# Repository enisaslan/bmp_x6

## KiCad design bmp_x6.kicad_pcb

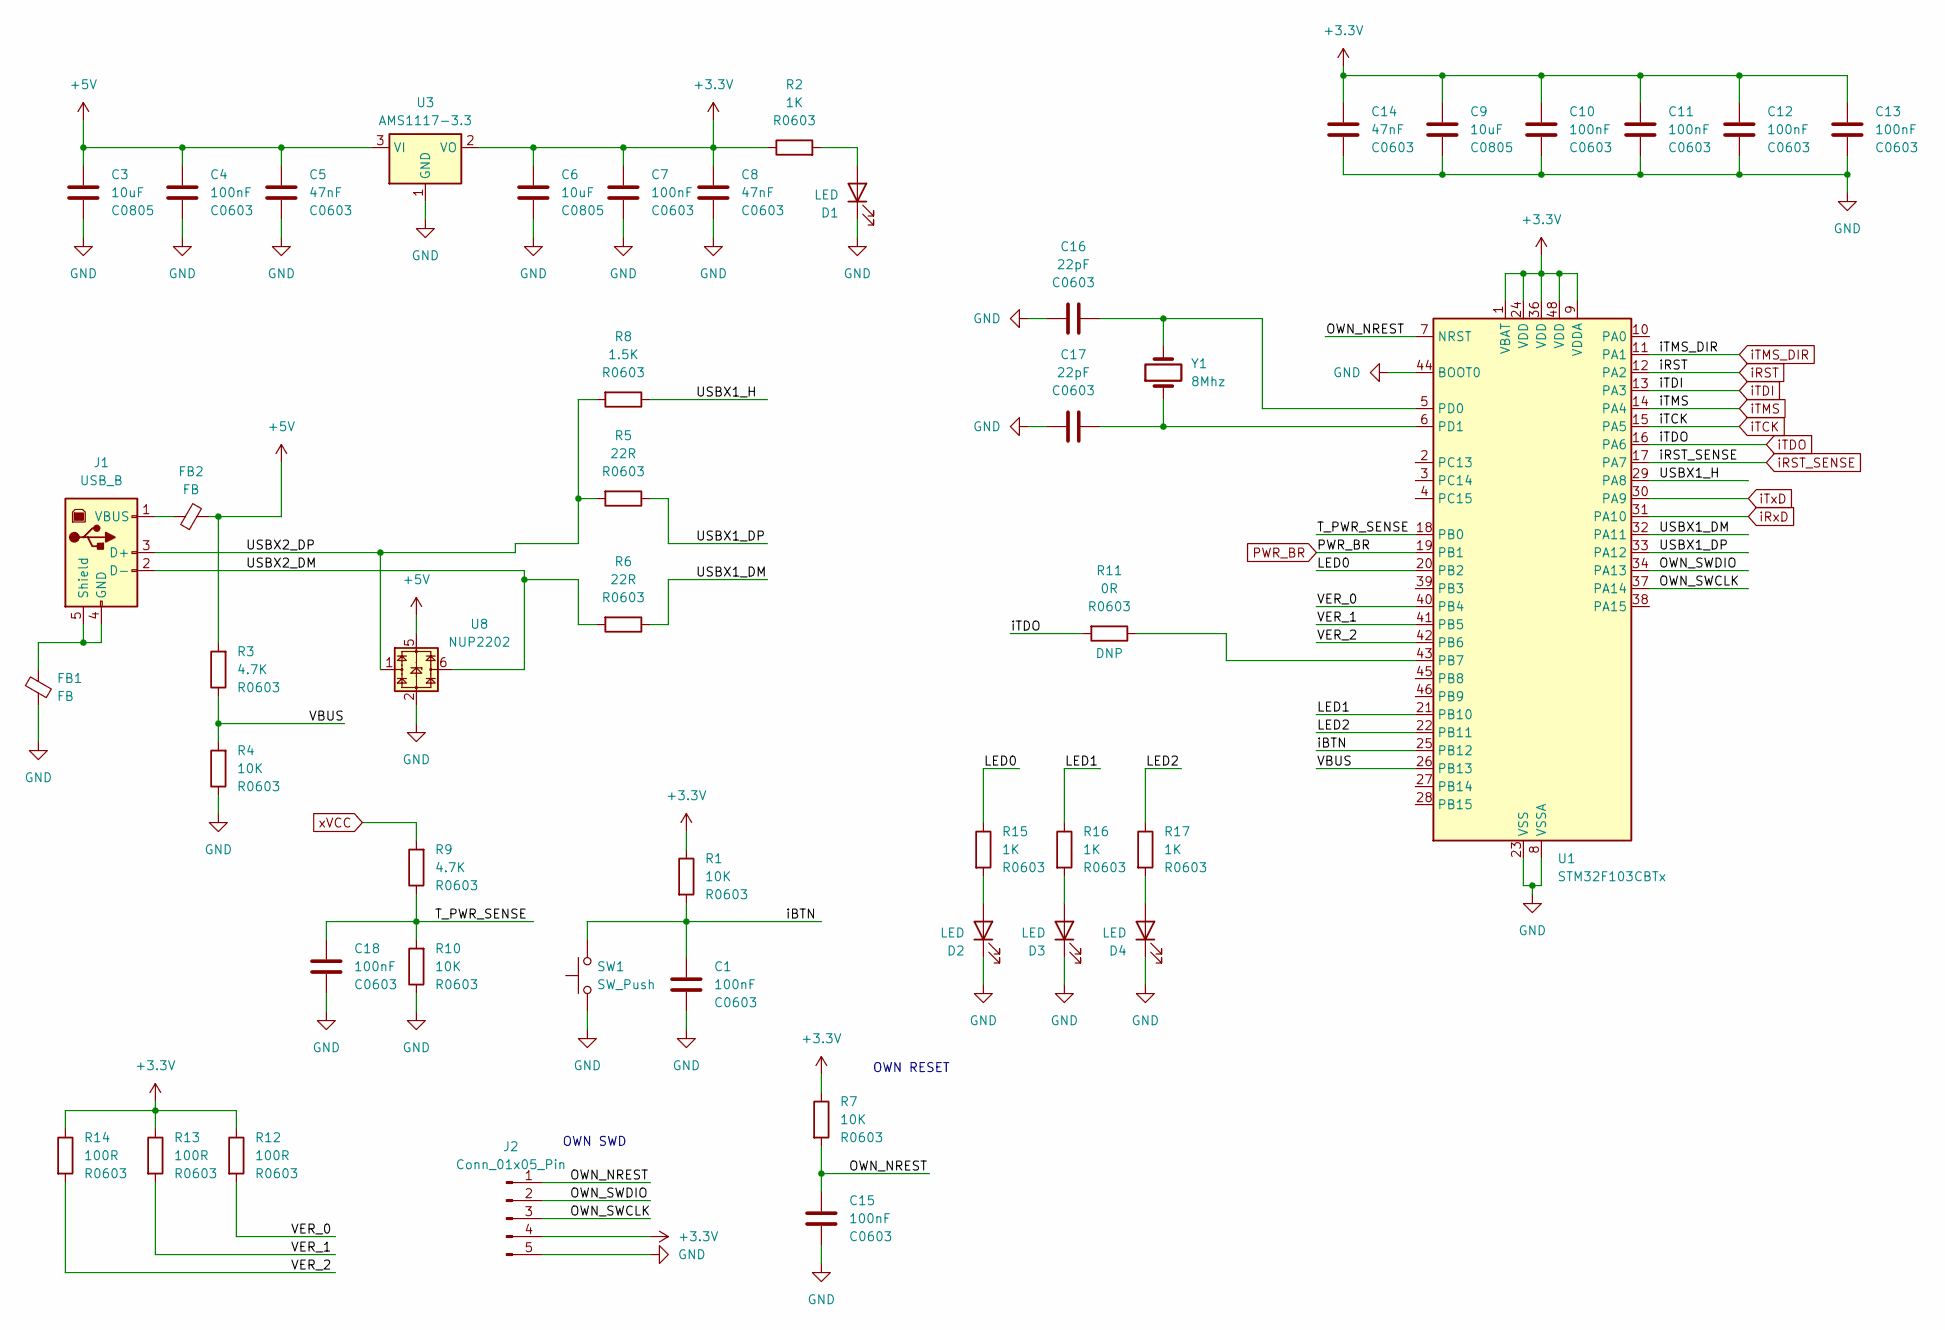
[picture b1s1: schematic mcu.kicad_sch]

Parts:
C1, C4, C7, C10, C11, C12, C13, C15, C18: 100nF; C_0603_1608Metric
C3, C6, C9: 10uF; C_0805_2012Metric
C5, C8, C14: 47nF; C_0603_1608Metric
C16, C17: 22pF; C_0603_1608Metric
D1, D2, D3, D4: LED; LED_0805_2012Metric
FB1, FB2: FB; L_0603_1608Metric
J1: USB_B; USB_B_Lumberg_2411_02_Horizontal
J2: Conn_01x05_Pin; PinHeader_1x05_P2.54mm_Vertical
R1, R4, R7, R10: 10K; R_0603_1608Metric
R2, R15, R16, R17: 1K; R_0603_1608Metric
R3, R9: 4.7K; R_0603_1608Metric
R5, R6: 22R; R_0603_1608Metric
R8: 1.5K; R_0603_1608Metric
R11: 0R; R_0603_1608Metric
R12, R13, R14: 100R; R_0603_1608Metric
SW1: SW_Push; SW_Tactile_SPST_Angled_PTS645Vx58-2LFS
U1: STM32F103CBTx; LQFP-48_7x7mm_P0.5mm
U3: AMS1117-3.3; SOT-223-3_TabPin2
U8: NUP2202; SOT-363_SC-70-6
Y1: 8Mhz; Crystal_SMD_Abracon_ABM3-2Pin_5.0x3.2mm

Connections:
+3.3V: C6.1, C7.1, C8.1, C9.1, C10.1, C11.1, C12.1, C13.1, C14.1, J2.4, R1.1, R2.1, R7.1, R12.1, R13.1, R14.1, U1.1 (VBAT), U1.9 (VDDA), U1.24 (VDD), U1.36 (VDD), U1.48 (VDD), U3.2 (VO); also elsewhere on the board
+5V: C3.1, C4.1, C5.1, FB2.2, R3.2, U3.3 (VI), U8.5
/mcu/LED0: R15.1, U1.20 (PB2)
/mcu/LED1: R16.1, U1.21 (PB10)
/mcu/LED2: R17.1, U1.22 (PB11)
/mcu/OWN_NREST: C15.1, J2.1, R7.2, U1.7 (NRST)
/mcu/OWN_SWCLK: J2.3, U1.37 (PA14)
/mcu/OWN_SWDIO: J2.2, U1.34 (PA13)
/mcu/T_PWR_SENSE: C18.1, R9.1, R10.2, U1.18 (PB0)
/mcu/USBX1_DM: R6.1, U1.32 (PA11)
/mcu/USBX1_DP: R5.1, U1.33 (PA12)
/mcu/USBX1_H: R8.1, U1.29 (PA8)
/mcu/USBX2_DM: J1.2 (D-), R6.2, U8.6
/mcu/USBX2_DP: J1.3 (D+), R5.2, R8.2, U8.1
/mcu/VBUS: R3.1, R4.2, U1.26 (PB13)
/mcu/VER_0: R12.2, U1.40 (PB4)
/mcu/VER_1: R13.2, U1.41 (PB5)
/mcu/VER_2: R14.2, U1.42 (PB6)
/mcu/iBTN: C1.1, R1.2, SW1.2, U1.25 (PB12)
GND: C1.2, C3.2, C4.2, C5.2, C6.2, C7.2, C8.2, C9.2, C10.2, C11.2, C12.2, C13.2, C14.2, C15.2, C16.2, C17.2, C18.2, D1.1 (K), D2.1 (K), D3.1 (K), D4.1 (K), FB1.2, J2.5, R4.1, R10.1, SW1.1, U1.8 (VSSA), U1.23 (VSS), U1.35 (VSS), U1.44 (BOOT0), U1.47 (VSS), U3.1 (GND), U8.2; also elsewhere on the board
unnamed: D1.2 (A), R2.2
unnamed: D2.2 (A), R15.2
unnamed: D3.2 (A), R16.2
unnamed: D4.2 (A), R17.2
unnamed: FB1.1, J1.4 (GND), J1.5 (Shield)
unnamed: FB2.1, J1.1 (VBUS)
unnamed: R11.1, U1.43 (PB7)
unnamed: C16.1, U1.5 (PD0), Y1.2
unnamed: C17.1, U1.6 (PD1), Y1.1
PWR_BR: U1.19 (PB1); also elsewhere on the board
iRST: U1.12 (PA2); also elsewhere on the board
iRST_SENSE: U1.17 (PA7); also elsewhere on the board
iRxD: U1.31 (PA10); also elsewhere on the board
iTCK: U1.15 (PA5); also elsewhere on the board
iTDI: U1.13 (PA3); also elsewhere on the board
iTDO: R11.2, U1.16 (PA6); also elsewhere on the board
iTMS: U1.14 (PA4); also elsewhere on the board
iTMS_DIR: U1.11 (PA1); also elsewhere on the board
iTxD: U1.30 (PA9); also elsewhere on the board
xVCC: R9.2; also elsewhere on the board

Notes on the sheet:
OWN RESET
OWN SWD

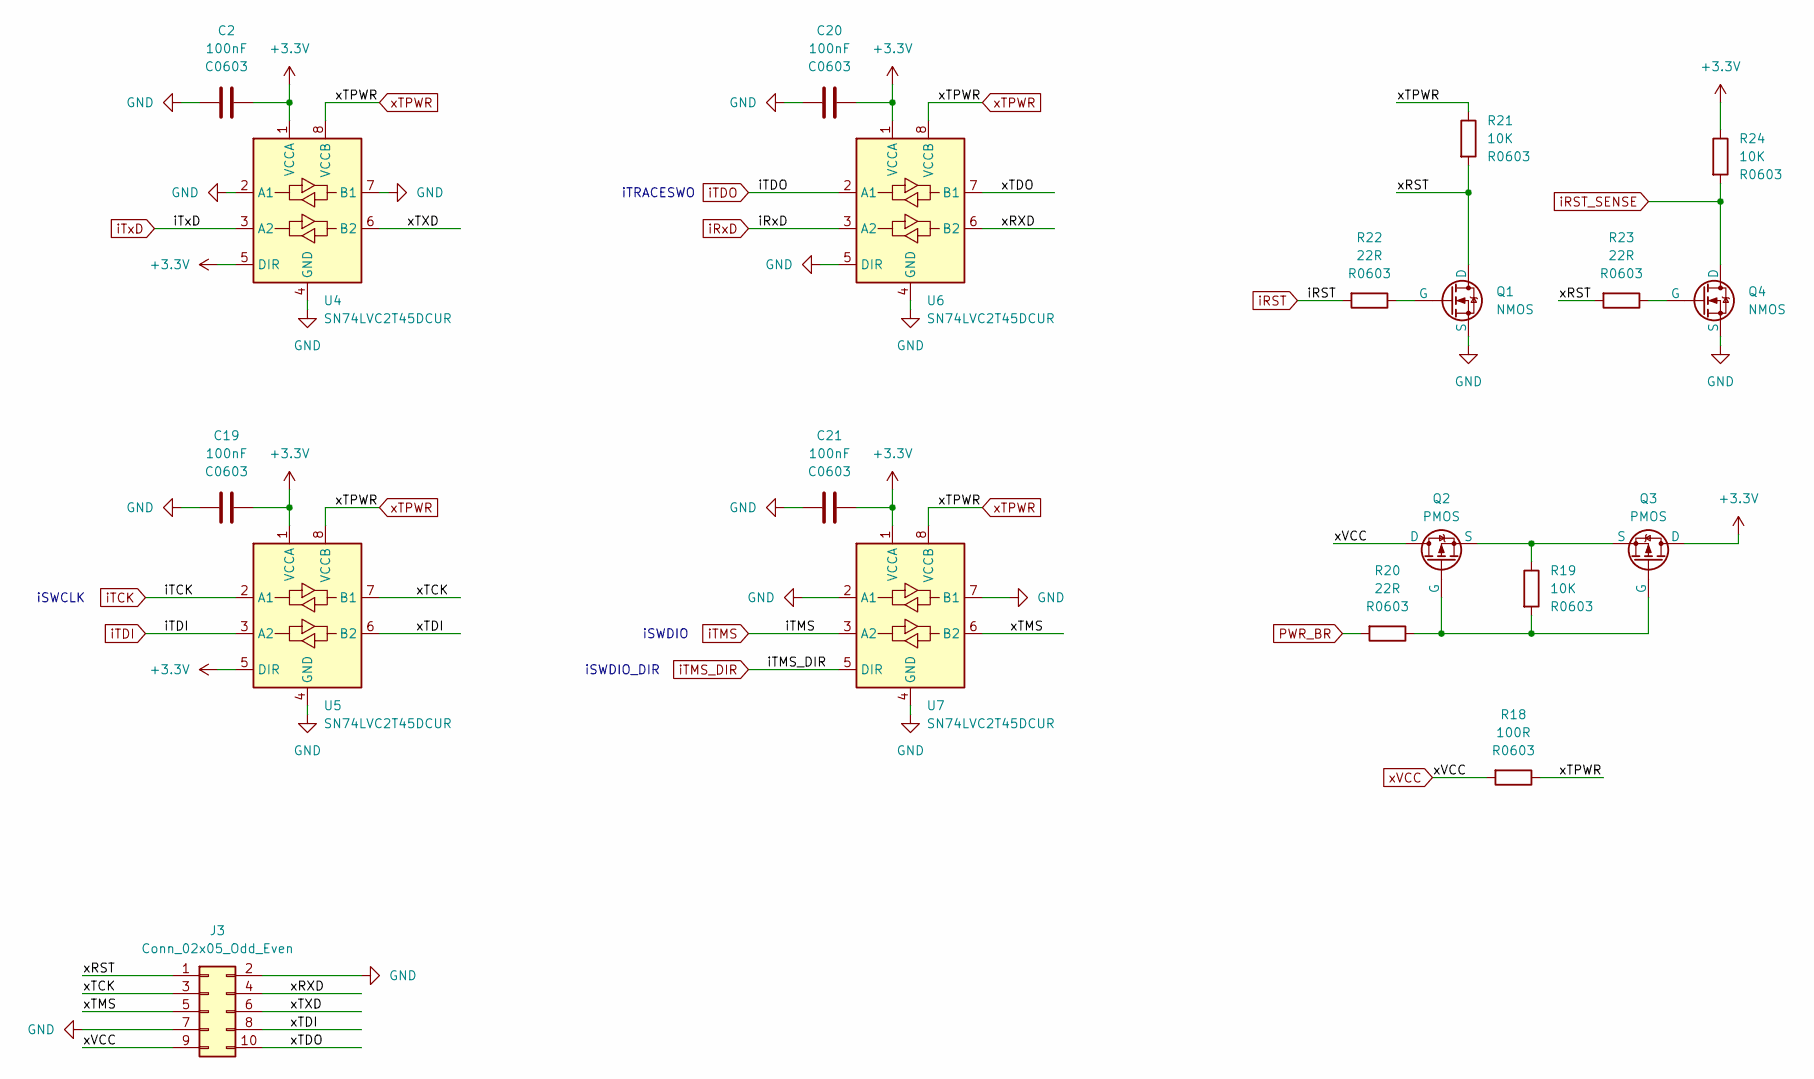
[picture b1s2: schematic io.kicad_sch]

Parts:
C2, C19, C20, C21: 100nF; C_0603_1608Metric
J3: Conn_02x05_Odd_Even; PinHeader_2x05_P2.54mm_Horizontal
Q1, Q4: NMOS; SOT-23-3
Q2, Q3: PMOS; SOT-23-3
R18: 100R; R_0603_1608Metric
R19, R21, R24: 10K; R_0603_1608Metric
R20, R22, R23: 22R; R_0603_1608Metric
U4, U5, U6, U7: SN74LVC2T45DCUR; VSSOP-8_2.3x2mm_P0.5mm

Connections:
+3.3V: C2.2, C19.2, C20.2, C21.2, Q3.1 (D), R24.1, U4.1 (VCCA), U4.5 (DIR), U5.1 (VCCA), U5.5 (DIR), U6.1 (VCCA), U7.1 (VCCA); also elsewhere on the board
/io/xRST: J3.1, Q1.1 (D), R21.2, R23.2
/io/xRXD: J3.4, U6.6 (B2)
/io/xTCK: J3.3, U5.7 (B1)
/io/xTDI: J3.8, U5.6 (B2)
/io/xTDO: J3.10, U6.7 (B1)
/io/xTMS: J3.5, U7.6 (B2)
/io/xTXD: J3.6, U4.6 (B2)
GND: C2.1, C19.1, C20.1, C21.1, J3.2, J3.7, Q1.3 (S), Q4.3 (S), U4.2 (A1), U4.4 (GND), U4.7 (B1), U5.4 (GND), U6.4 (GND), U6.5 (DIR), U7.2 (A1), U7.4 (GND), U7.7 (B1); also elsewhere on the board
unnamed: Q1.2 (G), R22.1
unnamed: Q2.2 (G), Q3.2 (G), R19.2, R20.1
unnamed: Q2.3 (S), Q3.3 (S), R19.1
unnamed: Q4.2 (G), R23.1
PWR_BR: R20.2; also elsewhere on the board
iRST: R22.2; also elsewhere on the board
iRST_SENSE: Q4.1 (D), R24.2; also elsewhere on the board
iRxD: U6.3 (A2); also elsewhere on the board
iTCK: U5.2 (A1); also elsewhere on the board
iTDI: U5.3 (A2); also elsewhere on the board
iTDO: U6.2 (A1); also elsewhere on the board
iTMS: U7.3 (A2); also elsewhere on the board
iTMS_DIR: U7.5 (DIR); also elsewhere on the board
iTxD: U4.3 (A2); also elsewhere on the board
xTPWR: R18.1, R21.1, U4.8 (VCCB), U5.8 (VCCB), U6.8 (VCCB), U7.8 (VCCB)
xVCC: J3.9, Q2.1 (D), R18.2; also elsewhere on the board

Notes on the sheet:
iSWDIO
iSWCLK
iSWDIO_DIR
iTRACESWO

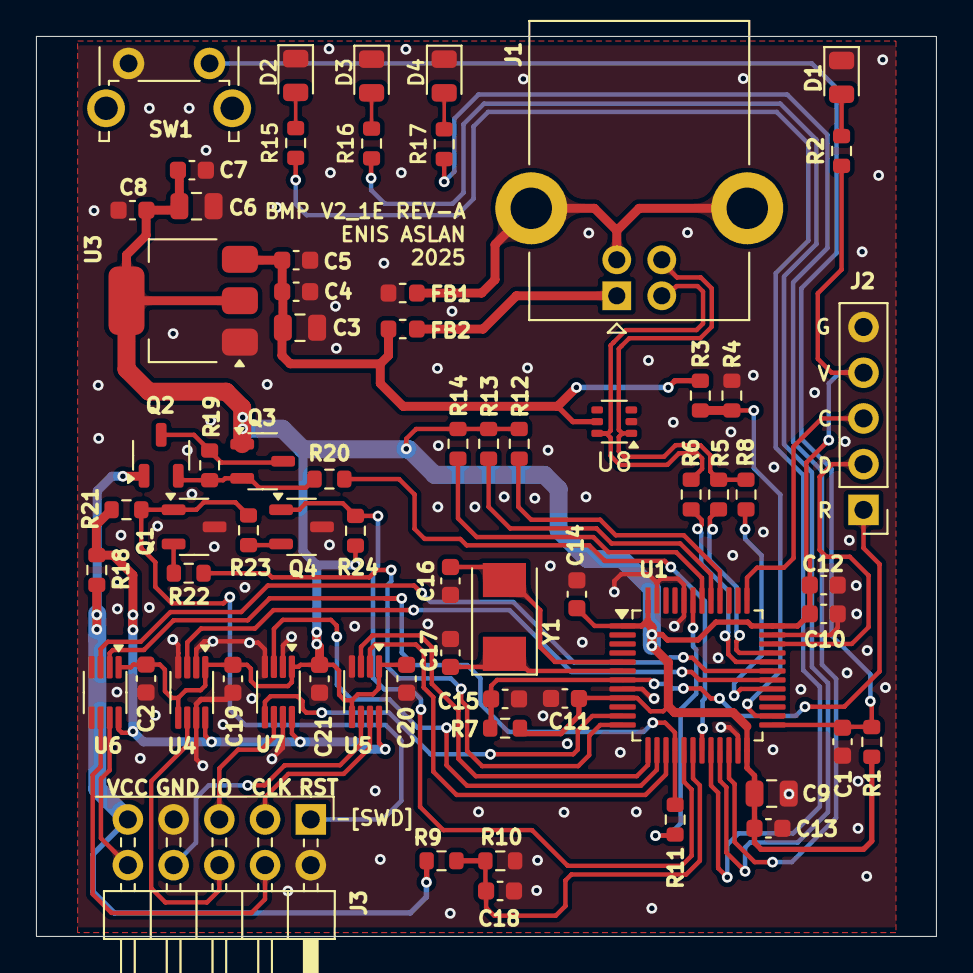
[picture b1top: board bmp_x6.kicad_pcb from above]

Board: 2 copper layers, 50.0 x 50.0 mm, 67 parts (0 on the bottom side), 52 nets.

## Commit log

2024-12-01 first upload. sch draw continue..
2024-12-01 update prject names and files.
2024-12-01 footprints update
2024-12-01 footprints update..
2024-12-01 backup folder removed.
2024-12-01 footprints update.
2024-12-01 pcb draw starting ..
2024-12-02 pcb components relocated.
2024-12-02 pcb drawing try
2024-12-03 shorcuts updated and components relocated.
2024-12-03 components relocated.
2024-12-03 drawing continue...
2024-12-04 drawing continue..
2024-12-04 drw continue..
2024-12-05 drw continue...
2024-12-06 pcb drw continue...
2024-12-06 shortcuts updated
2024-12-07 silkscreen updated.
2024-12-09 ground plane ok.
2024-12-23 silk font&size updated.
2025-05-19 opened with KiCad 9.0.2
2025-09-30 order data git add .!
